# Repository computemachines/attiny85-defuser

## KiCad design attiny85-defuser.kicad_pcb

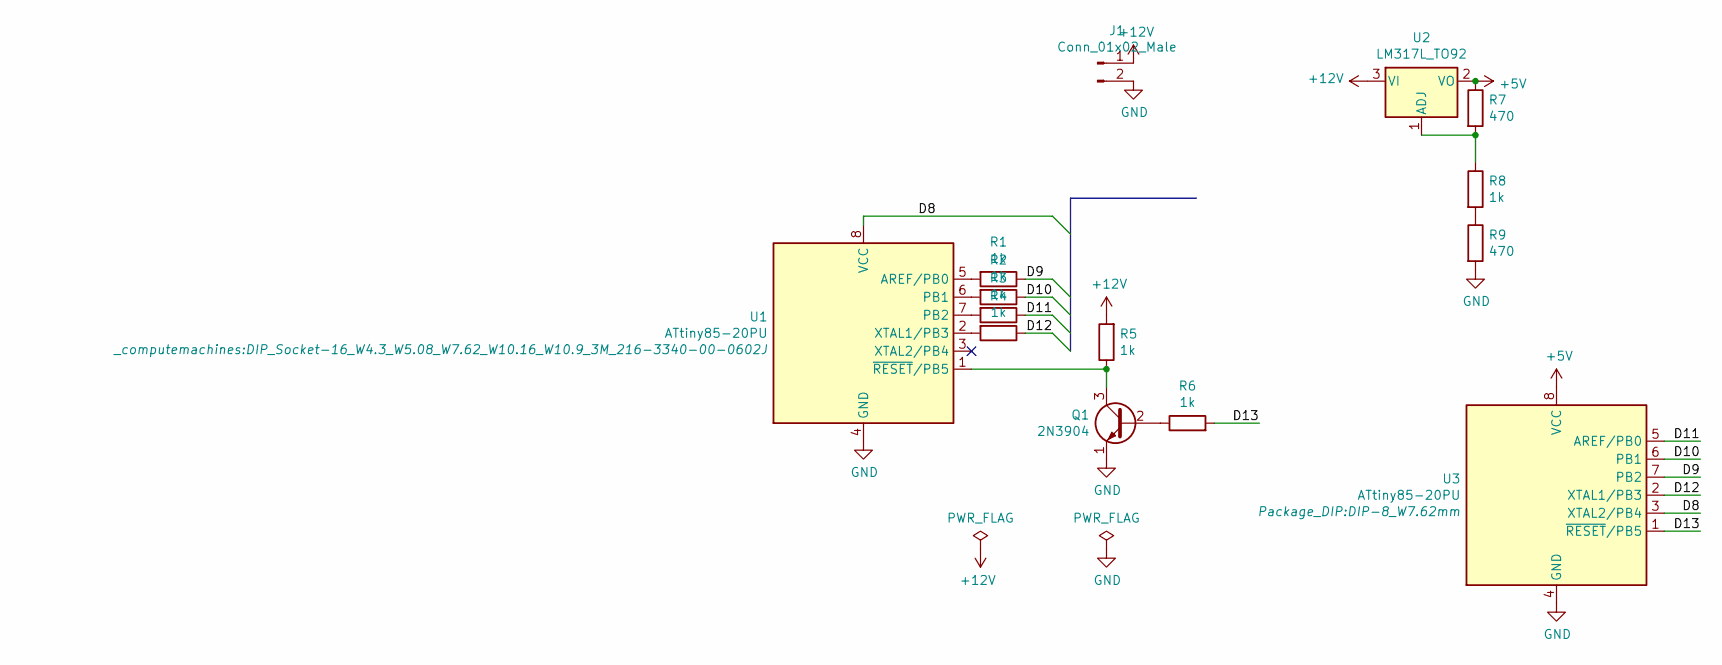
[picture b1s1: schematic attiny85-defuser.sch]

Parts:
J1: Conn_01x02_Male; PinHeader_1x02_P2.54mm_Vertical
Q1: 2N3904; TO-92_Inline
R1, R2, R3, R4, R5, R6, R8: 1k; R_Axial_DIN0207_L6.3mm_D2.5mm_P10.16mm_Horizontal
R7, R9: 470; R_Axial_DIN0207_L6.3mm_D2.5mm_P10.16mm_Horizontal
U1: ATtiny85-20PU; DIP_Socket-16_W4.3_W5.08_W7.62_W10.16_W10.9_3M_216-3340-00-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
U2: LM317L_TO92; TO-92_Inline
U3: ATtiny85-20PU; DIP-8_W7.62mm

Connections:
+5V: R7.1, U2.2 (VO), U3.8 (VCC)
+12V: J1.1, R5.2, U2.3 (VI)
/D8: U1.8 (VCC), U3.3 (XTAL2/PB4)
/D9: R1.1, U3.7 (PB2)
/D10: R2.1, U3.6 (PB1)
/D11: R3.1, U3.5 (AREF/PB0)
/D12: R4.1, U3.2 (XTAL1/PB3)
/D13: R6.2, U3.1 (~RESET~/PB5)
GND: J1.2, Q1.1 (E), R9.2, U1.4 (GND), U3.4 (GND)
unnamed: Q1.2 (B), R6.1
unnamed: Q1.3 (C), R5.1, U1.1 (~RESET~/PB5)
unnamed: R1.2, U1.5 (AREF/PB0)
unnamed: R2.2, U1.6 (PB1)
unnamed: R3.2, U1.7 (PB2)
unnamed: R4.2, U1.2 (XTAL1/PB3)
unnamed: R7.2, R8.1, U2.1 (ADJ)
unnamed: R8.2, R9.1

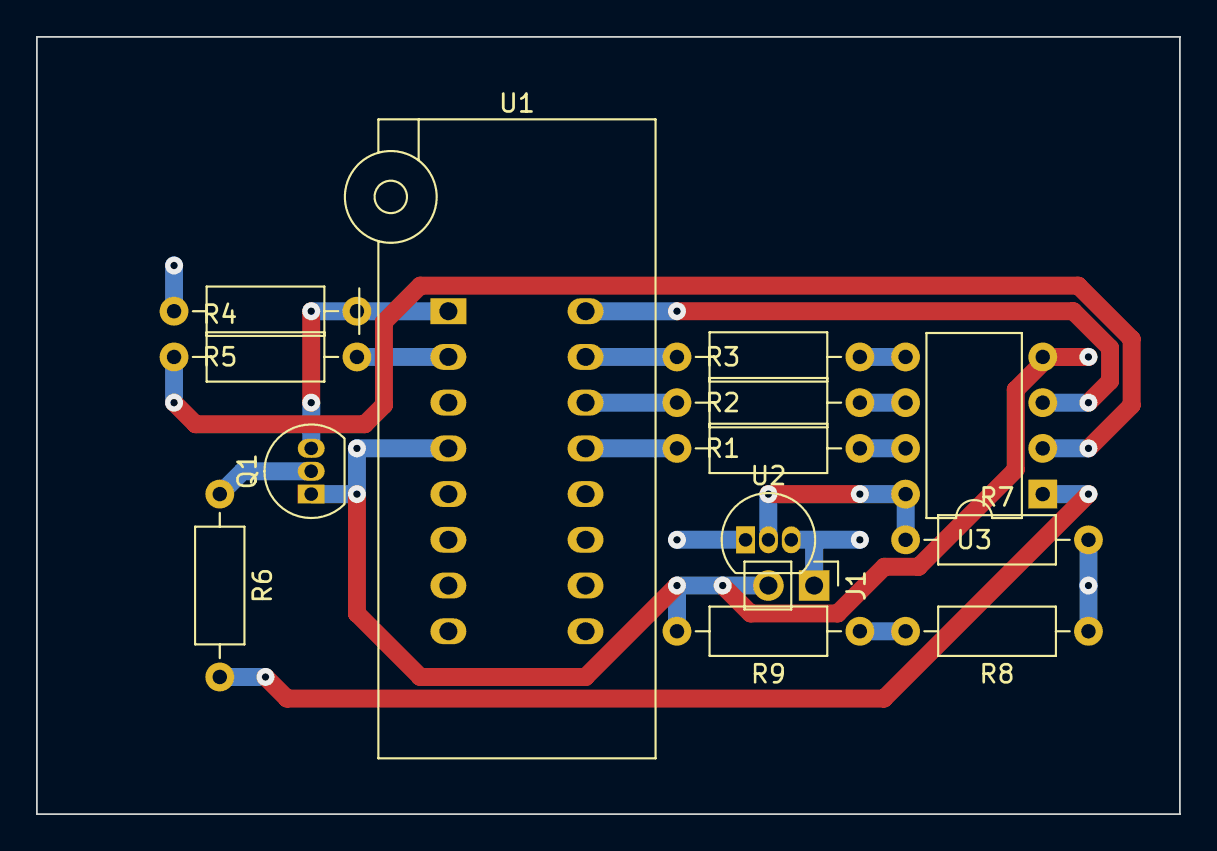
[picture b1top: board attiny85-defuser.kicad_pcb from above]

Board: 4 copper layers, 63.5 x 43.2 mm, 14 parts (0 on the bottom side), 17 nets.
